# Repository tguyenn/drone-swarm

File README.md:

# Drone Swarm

This project is going to be a fully DIY drone swarm project based around ESP32 connectivity. There will be an ESP32 based handheld controller that will connect to ESP32 based drones over ESPNOW.

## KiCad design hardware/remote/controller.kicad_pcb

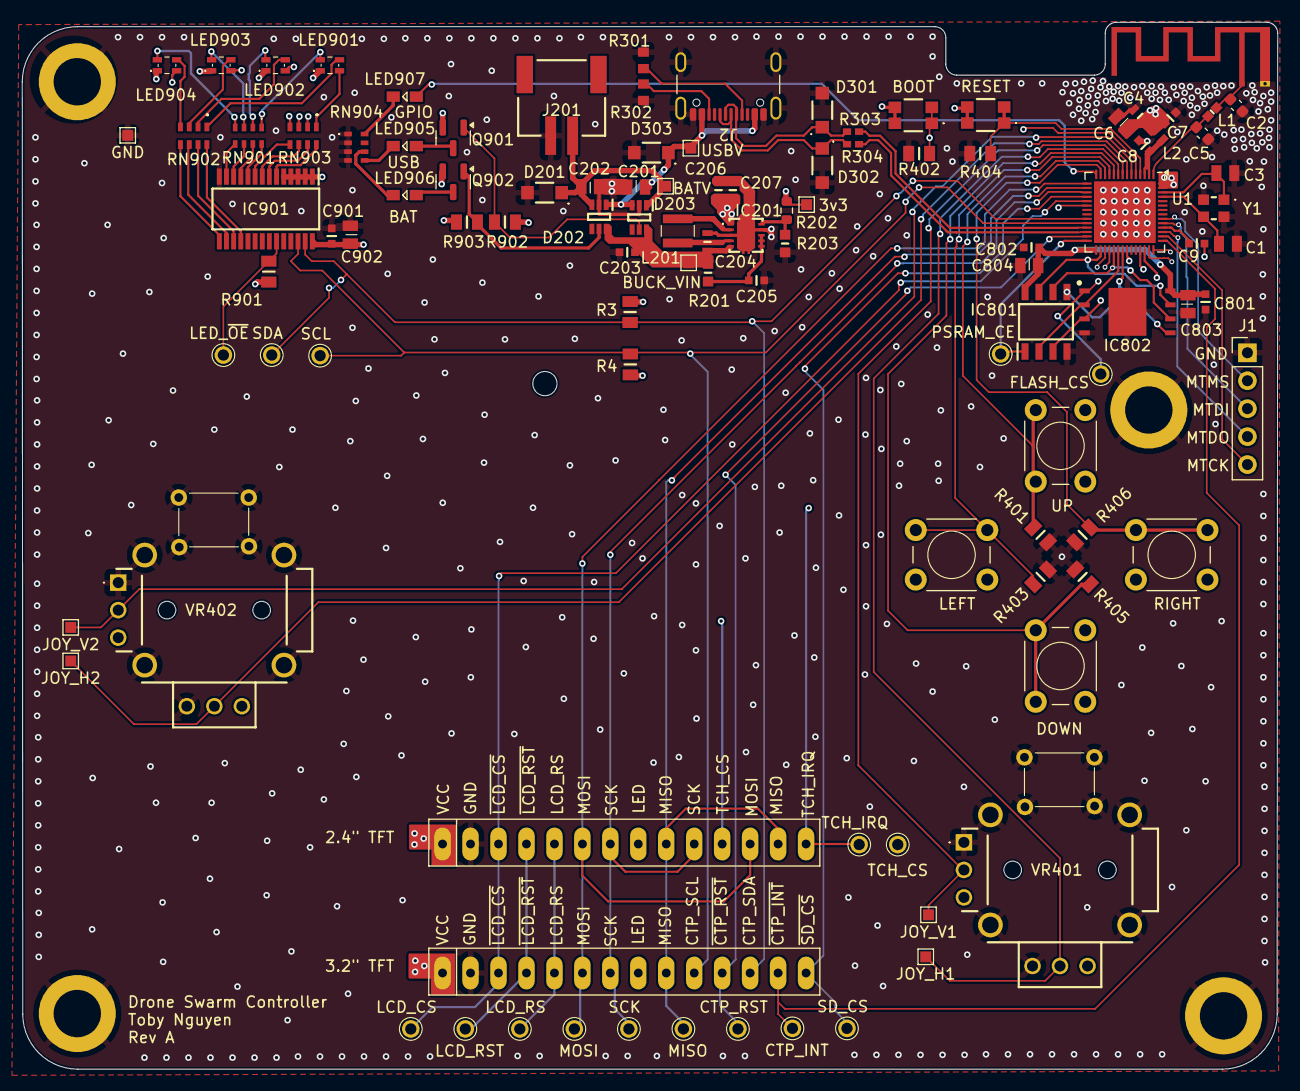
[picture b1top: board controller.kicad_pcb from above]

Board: 4 copper layers, 114.0 x 95.1 mm, 113 parts (0 on the bottom side), 90 nets.

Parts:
AE1: Antenna_Chip; Texas_SWRA117D_2.4GHz_Left
C1, C3: 10p; CAPC2013X94N
C2, C5: 1p8; C_0603_1608Metric
C4, C204, C206, C207: 10u; CAPC1608X80N
C6, C201, C202, C803, C804, C902: 1u; CAPC2012X135N
C7, C8, C9, C203, C205, C801, C802, C901: u1; MAJx16
D201, D301, D302, D303: SMF5.0A_R1_00001; SMF50A_R1_00001
D202, D203: LM66100DCKR; SOP65P210X110-6N
H101: MountingHole; MountingHole_2.2mm_M2_DIN965
H102, H103, H104, H105: MountingHole_Pad; MountingHole_4.3mm_M4_ISO14580_Pad
IC201: TPS63000IDRCRQ1
IC801: 4677; SOIC127P600X175-8N
IC802: W25Q256JVEIQ; SON127P800X600X80-9N-D
IC901: PCA9685PW_Q900,118; SOP65P640X110-28N
J1: Conn_01x05_Pin; PinHeader_1x05_P2.54mm_Vertical
J2: USB_C_Receptacle_USB2.0_16P; USB_C_Receptacle_GCT_USB4105-xx-A_16P_TopMnt_Horizontal
J201: JST-PH Conn; 1769
L1: 3nH; INDC1006X65N
L2: 2nH; WE-KI_0603A30
L201: 2u2; NRS3015T2R2MNGHV
LED901, LED902, LED903, LED904: SM0605RGB
LED905, LED906, LED907: Orange; LEDM2214X140N
NT201: NetTie; NetTie-2_Pad0.3mm
Q901, Q902: IRLML6402TRPBF; SOT-23
R3, R4, R401, R402, R403, R404, R405, R406, R901, R902, R903: 10k; RESC2012X60N
R201: 100; RESC1608X55N
R202: 1M; R_0603_1608Metric
R203: 200k; RESC1608X55N
R301, R302: 5k1; RESC1608X50N
R303, R304: 27; RESC1005X40N
RN901, RN904: 150 Ohms; EXBV8V151JV
RN902, RN903: 100 Ohms; EXBU38
S401: BOOT; TL1030AF500AQJ
S402: RESET; TL1030AF500AQJ
SW401: UP; SW_PUSH_6mm
SW402: LEFT; SW_PUSH_6mm
SW403: DOWN; SW_PUSH_6mm
SW404: RIGHT; SW_PUSH_6mm
TP3: MOSI; 5000
TP5: SDA; 5000
TP6: MISO; 5000
TP8: SCL; 5000
TP9: SCK; 5000
TP10: CTP_RST; 5000
TP11: SD_CS; 5000
TP12: CTP_INT; 5000
TP13: LCD_CS; 5000
TP14: LED_~{OE}; 5000
TP15: LCD_RST; 5000
TP16: LCD_RS; 5000
TP17: TCH_CS; 5000
TP18: TCH_IRQ; 5000
TP201: BATV; TestPoint_Pad_1.0x1.0mm
TP202: GND; TestPoint_Pad_1.0x1.0mm
TP203: 3v3; TestPoint_Pad_1.0x1.0mm
TP204: USBV; TestPoint_Pad_1.0x1.0mm
TP205: BUCK_VIN; TestPoint_Pad_1.0x1.0mm
TP401: JOY_V1; TestPoint_Pad_1.0x1.0mm
TP402: JOY_H1; TestPoint_Pad_1.0x1.0mm
TP403: JOY_V2; TestPoint_Pad_1.0x1.0mm
TP404: JOY_H2; TestPoint_Pad_1.0x1.0mm
TP801: PSRAM_CE; 5000
TP802: FLASH_CS; 5000
U1: ESP32-S3; QFN-56-1EP_7x7mm_P0.4mm_EP5.6x5.6mm
U501, U502: 3.2inch_IPS_SPI_Module_ILI9341; TFT-320x240
VR401, VR402: RKJXV1224005
Y1: FH4000074Z

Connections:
+3V3: C4.1, C6.1, C7.1, C9.1, C206.1, C207.1, C901.1, C902.1, IC201.1 (VOUT), IC901.1 (A0), IC901.2 (A1), IC901.3 (A2), IC901.4 (A3), IC901.5 (A4), IC901.28 (VDD), L2.1, LED901.1 (ANODE), LED902.1 (ANODE), LED903.1 (ANODE), LED904.1 (ANODE), Q901.2 (S), Q902.2 (S), R3.2, R4.2, R202.1, R901.1, R902.2, R903.2, S401.2, S402.2, SW401.2, SW402.2, SW403.2, SW404.2, TP203.1, U1.20 (VDD3P3_RTC), U1.55 (VDDA), U1.56 (VDDA), U501.1 (VCC), U502.1 (VCC), VR401.A3 (CW_1), VR401.B3 (CW_2), VR402.A3 (CW_1), VR402.B3 (CW_2)
/ESP32/BUT_JOY.BUT_BOOT: R402.1, S401.1, U1.5 (GPIO0/BOOT)
/ESP32/BUT_JOY.BUT_DOWN: R405.1, SW403.1, U1.10 (GPIO5/ADC1_CH4)
/ESP32/BUT_JOY.BUT_LEFT: R403.1, SW402.1, U1.11 (GPIO6/ADC1_CH5)
/ESP32/BUT_JOY.BUT_RESET: R404.1, S402.1, U1.4 (CHIP_PU/RESET)
/ESP32/BUT_JOY.BUT_RIGHT: R406.1, SW404.1, U1.13 (GPIO8/ADC1_CH7)
/ESP32/BUT_JOY.BUT_UP: R401.1, SW401.1, U1.12 (GPIO7/ADC1_CH6)
/ESP32/BUT_JOY.JOY1_H: TP402.1, U1.9 (GPIO4/ADC1_CH3), VR401.B2 (WIPER_2)
/ESP32/BUT_JOY.JOY1_V: TP401.1, U1.8 (GPIO3/ADC1_CH2), VR401.A2 (WIPER_1)
/ESP32/BUT_JOY.JOY2_H: TP404.1, U1.7 (GPIO2/ADC1_CH1), VR402.B2 (WIPER_2)
/ESP32/BUT_JOY.JOY2_V: TP403.1, U1.6 (GPIO1/ADC1_CH0), VR402.A2 (WIPER_1)
/ESP32/I2C_CTP_LED.CTP_INT: TP12.1, U1.43 (GPIO38), U501.13 (~CTP_INT)
/ESP32/I2C_CTP_LED.CTP_RST: TP10.1, U1.27 (GPIO21), U501.11 (~CTP_RST)
/ESP32/I2C_CTP_LED.SCL: IC901.26 (SCL), R4.1, TP8.1, U1.24 (GPIO18/ADC2_CH7), U501.10 (CTP_SCL)
/ESP32/I2C_CTP_LED.SDA: IC901.27 (SDA), R3.1, TP5.1, U1.23 (GPIO17/ADC2_CH6), U501.12 (CTP_SDA)
/ESP32/I2C_CTP_LED.~OE: IC901.23 (~OE), R901.2, TP14.1, U1.36 (SPICLK_N/GPIO48)
/ESP32/LED_GPIO: LED907.2 (A), U1.14 (GPIO9/ADC1_CH8)
/ESP32/MEM.SCK: IC801.6 (SCLK), IC802.6 (CLK), U1.33 (SPICLK/GPIO30)
/ESP32/MEM.SIO0: IC801.5 (SI/SIO[0]), IC802.5 (DI_(IO0)), U1.35 (SPID/GPIO32)
/ESP32/MEM.SIO1: IC801.2 (SO/SIO[1]), IC802.2 (DO_(IO1)_1), U1.34 (SPIQ/GPIO31)
/ESP32/MEM.SIO2: IC801.3 (SIO[2]), IC802.3 (DO_(IO1)_2), U1.31 (SPIWP/GPIO28)
/ESP32/MEM.SIO3: IC801.7 (SIO[3]), IC802.7 (IO3), U1.30 (SPIHD/GPIO27)
/ESP32/MEM.~CE: IC801.1 (CE#), TP801.1, U1.28 (SPI_CS1/GPIO26)
/ESP32/MEM.~CS: IC802.1 (/CS), TP802.1, U1.32 (SPICS0/GPIO29)
/ESP32/MTCK: J1.5, U1.44 (MTCK/JTAG/GPIO39)
/ESP32/MTDI: J1.3, U1.47 (MTDI/JTAG/GPIO41)
/ESP32/MTDO: J1.4, U1.45 (MTDO/JTAG/GPIO40)
/ESP32/MTMS: J1.2, U1.48 (MTMS/JTAG/GPIO42)
/ESP32/SPI_LCD_SD.LCD_CS: TP13.1, U1.19 (GPIO14/ADC2_CH3), U501.3 (~LCD_CS), U502.3 (~LCD_CS)
/ESP32/SPI_LCD_SD.LCD_RS: TP16.1, U1.42 (GPIO37), U501.5 (LCD_RS), U502.5 (LCD_RS)
/ESP32/SPI_LCD_SD.LCD_RST: TP15.1, U1.41 (GPIO36), U501.4 (~LCD_RST), U502.4 (~LCD_RST)
/ESP32/SPI_LCD_SD.MISO: TP6.1, U1.16 (GPIO11/ADC2_CH0), U501.9 (MISO), U502.9 (MISO), U502.13 (T_DO)
/ESP32/SPI_LCD_SD.MOSI: TP3.1, U1.15 (GPIO10/ADC1_CH9), U501.6 (MOSI), U502.6 (MOSI), U502.12 (T_DIN)
/ESP32/SPI_LCD_SD.SCK: TP9.1, U1.17 (GPIO12/ADC2_CH1), U501.7 (SCK), U502.7 (SCK), U502.10 (T_CLK)
/ESP32/SPI_LCD_SD.SD_CS: TP11.1, U1.18 (GPIO13/ADC2_CH2), U501.14 (~SD_CS)
/ESP32/SPI_LCD_SD.TCH_CS: TP17.1, U1.40 (GPIO35), U502.11 (T_CS)
/ESP32/SPI_LCD_SD.TCH_IRQ: TP18.1, U1.39 (GPIO34), U502.14 (T_IRQ)
/ESP32/USB+: R304.2, U1.26 (GPIO20/USB_D+/ADC2_CH9)
/ESP32/USB-: R303.2, U1.25 (GPIO19/USB_D-/ADC2_CH8)
/LEDS/B1: LED901.2 (C_BLUE), RN903.1
/LEDS/B2: LED902.2 (C_BLUE), RN903.2
/LEDS/B3: LED903.2 (C_BLUE), RN903.3
/LEDS/B4: LED904.2 (C_BLUE), RN903.4
/LEDS/BAT_ST: D203.5 (ST), Q901.1 (G), R902.1
/LEDS/C_BLU1: IC901.6 (LED0), RN903.8
/LEDS/C_BLU2: IC901.7 (LED1), RN903.7
/LEDS/C_BLU3: IC901.8 (LED2), RN903.6
/LEDS/C_BLU4: IC901.9 (LED3), RN903.5
/LEDS/C_GRN1: IC901.18 (LED11), RN902.8
/LEDS/C_GRN2: IC901.17 (LED10), RN902.7
/LEDS/C_GRN3: IC901.16 (LED9), RN902.6
/LEDS/C_GRN4: IC901.15 (LED8), RN902.5
/LEDS/C_RED1: IC901.10 (LED4), RN901.8
/LEDS/C_RED2: IC901.11 (LED5), RN901.7
/LEDS/C_RED3: IC901.12 (LED6), RN901.6
/LEDS/C_RED4: IC901.13 (LED7), RN901.5
/LEDS/G1: LED901.4 (C_GREEN), RN902.1
/LEDS/G2: LED902.4 (C_GREEN), RN902.2
/LEDS/G3: LED903.4 (C_GREEN), RN902.3
/LEDS/G4: LED904.4 (C_GREEN), RN902.4
/LEDS/R1: LED901.3 (C_RED), RN901.1
/LEDS/R2: LED902.3 (C_RED), RN901.2
/LEDS/R3: LED903.3 (C_RED), RN901.3
/LEDS/R4: LED904.3 (C_RED), RN901.4
/LEDS/USBC_ST: D202.5 (ST), Q902.1 (G), R903.1
/POWER/BAT_VBUS: C202.1, D201.1 (K), D202.3 (~CE), D203.1 (VIN), J201.1, TP201.1
/POWER/BUCK_VIN: C203.1, C204.1, D202.6 (VOUT), D203.6 (VOUT), IC201.5 (VIN), R201.1, TP205.1
/POWER/USBC_VBUS: C201.1, D202.1 (VIN), D203.3 (~CE), D303.1 (K), J2.A4 (VBUS), J2.A9 (VBUS), J2.B4 (VBUS), J2.B9 (VBUS), TP204.1
/USBC/CC1: J2.A5 (CC1), R301.1
/USBC/CC2: J2.B5 (CC2), R302.1
/USBC/D+: D302.1 (K), J2.A6 (D+), J2.B6 (D+), R304.1
/USBC/D-: D301.1 (K), J2.A7 (D-), J2.B7 (D-), R303.1
GND: AE1.2 (PCB_Trace), C1.2, C2.2, C3.2, C4.2, C5.2, C6.2, C7.2, C8.2, C201.2, C202.2, C203.2, C205.2, C801.2, C802.2, C803.2, C804.2, C901.2, C902.2, D201.2 (A), D202.2 (GND), D203.2 (GND), D301.2 (A), D302.2 (A), D303.2 (A), H102.1, H103.1, H104.1, H105.1, IC201.9 (GND), IC801.4 (VSS), IC802.4 (GND), IC802.9 (EP), IC901.14 (VSS), J1.1, J2.A1 (GND), J2.A12 (GND), J2.B1 (GND), J2.B12 (GND), J2.S1 (SHIELD), J201.2, NT201.1, R203.2, R301.2, R302.2, R401.2, R402.2, R403.2, R404.2, R405.2, R406.2, RN904.1, RN904.2, RN904.3, RN904.4, TP202.1, U1.57 (GND), U501.2 (GND), U502.2 (GND), VR401.1 (MH1), VR401.2 (MH2), VR401.3 (MH3), VR401.4 (MH4), VR401.5 (BUT_0), VR401.6 (BUT_1), VR401.A1 (CCW_1), VR401.B1 (CCW_2), VR402.1 (MH1), VR402.2 (MH2), VR402.3 (MH3), VR402.4 (MH4), VR402.5 (BUT_0), VR402.6 (BUT_1), VR402.A1 (CCW_1), VR402.B1 (CCW_2), Y1.2 (GND), Y1.4 (GND)
GNDPWR: C204.2, C206.2, C207.2, IC201.3 (PGND_1), IC201.11 (PGND_2), IC201.12 (PGND_3), IC201.13 (PGND_4), IC201.14 (PGND_5), IC201.15 (PGND_6), NT201.2
unnamed: AE1.1 (FEED), C2.1, L1.1
unnamed: C205.1, IC201.6 (EN), IC201.7 (PS/SYNC), IC201.8 (VINA), R201.2
unnamed: IC201.10 (FB), R202.2, R203.1
unnamed: IC201.4 (L1), L201.1
unnamed: IC201.2 (L2), L201.2
unnamed: LED905.2 (A), Q901.3 (D)
unnamed: LED905.1 (K), RN904.5
unnamed: LED906.2 (A), Q902.3 (D)
unnamed: LED906.1 (K), RN904.6
unnamed: LED907.1 (K), RN904.8
unnamed: C5.1, L1.2, U1.1 (LNA_IN/RF)
unnamed: C9.2, U1.46 (VDD3P3_CPU)
unnamed: C1.1, U1.53 (XTAL_N), Y1.3 (XOUT)
unnamed: C3.1, U1.54 (XTAL_P), Y1.1 (XIN)
VDD3P3: C8.1, L2.2, U1.2 (VDD3P3), U1.3 (VDD3P3)
VDD_SPI: C801.1, C802.1, C803.1, C804.1, IC801.8 (VCC), IC802.8 (VCC), U1.29 (VDD_SPI)

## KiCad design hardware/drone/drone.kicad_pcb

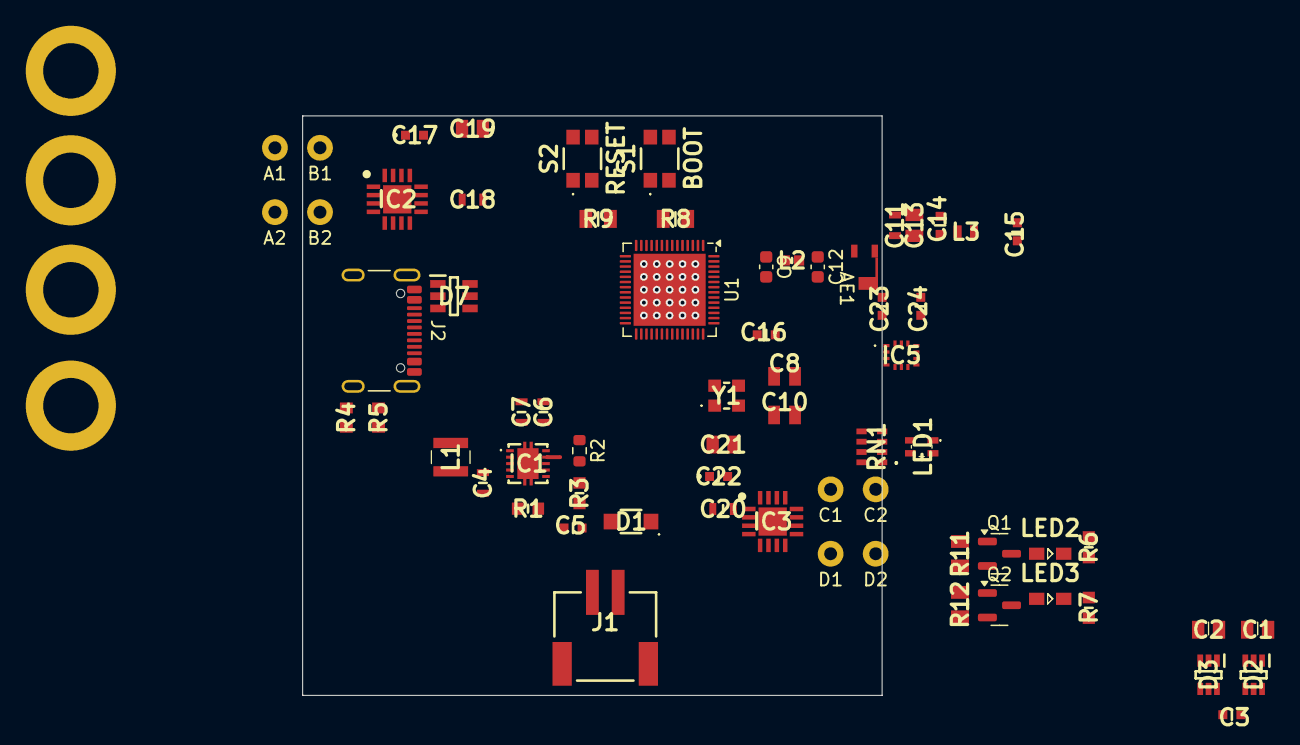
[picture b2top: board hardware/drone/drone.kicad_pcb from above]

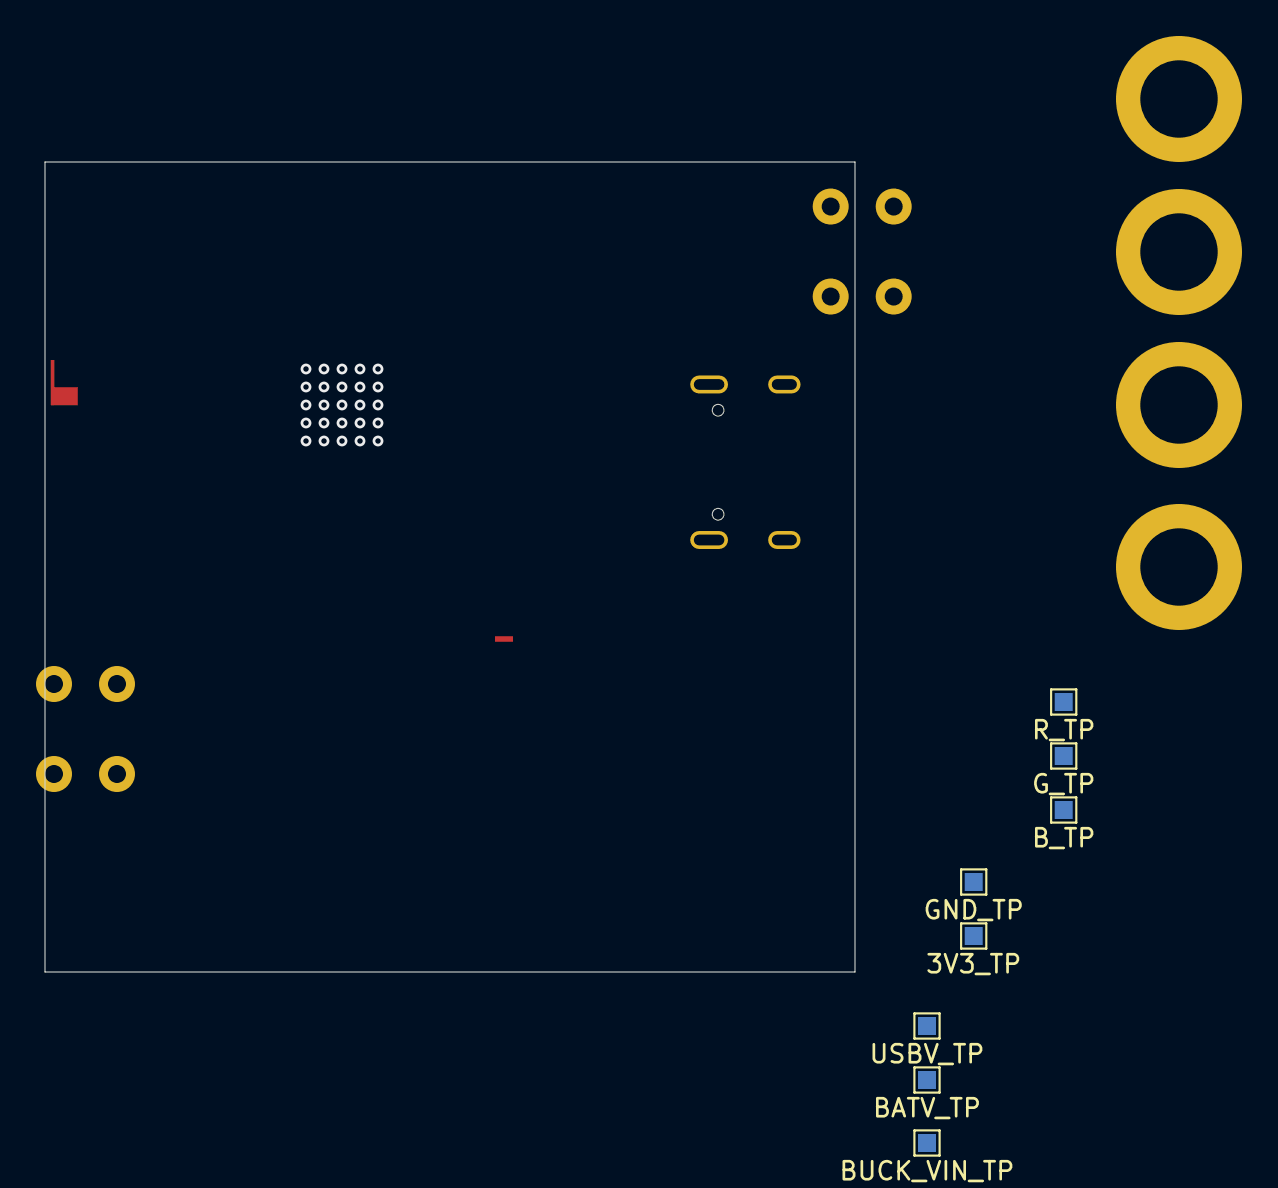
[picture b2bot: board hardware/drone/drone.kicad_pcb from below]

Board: 4 copper layers, 45.0 x 45.0 mm, 80 parts (8 on the bottom side), 62 nets, no tracks yet.

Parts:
AE1: Antenna_Chip; AANI-CH-0133
C1, C2, C13: 1u; CAPC2012X135N
C3, C5, C14, C15, C16, C23, C24: u1; MAJx16
C4, C6, C7, C11, C18, C20: 10u; CAPC1608X80N
C8, C10: 10p; CAPC2013X94N
C9, C12: 1p8; C_0603_1608Metric
C17, C22: 2u2; MBASx168
C19, C21: 10n; CAPC2012X90N
D1: SMF5.0A_R1_00001; SMF50A_R1_00001
D2, D3: LM66100DCKR; SOP65P210X110-6N
D7: USBLC6-4SC6Y; SOT95P280X145-6N
H2, H3, H4, H5: MountingHole_Pad; MountingHole_4.3mm_M4_ISO14580_Pad
IC1: TPS63000IDRCRQ1
IC2, IC3: DRV8833RTYR; QFN65P400X400X80-17N-D
IC5: BMI323
J1: 1769
J2: USB_C_Receptacle_GCT_USB4105-xx-A_16P_TopMnt_Horizontal
L1: 2u2; NRS3015T2R2MNGHV
L2: 3nH; INDC1006X65N
L3: 2nH; WE-KI_0603A30
LED1: SM0605RGB
LED2, LED3: LO_M676-Q2S1-24-Z; LEDM2214X140N
NT1: NetTie; custom_net_tie
Q1, Q2: IRLML6402TRPBF; SOT-23
R1, R6, R7: 100; RESC1608X55N
R2: 1M; R_0603_1608Metric
R3: 200k; RESC1608X55N
R4, R5: 5k1; RESC1608X50N
R8, R9, R11, R12: 10k; RESC2012X60N
RN1: 100 Ohms; EXBU38
S1: BOOT; TL1030AF500AQJ
S2: RESET; TL1030AF500AQJ
TP1: USBV_TP; TestPoint_Pad_1.0x1.0mm
TP2: BATV_TP; TestPoint_Pad_1.0x1.0mm
TP3: BUCK_VIN_TP; TestPoint_Pad_1.0x1.0mm
TP4: GND_TP; TestPoint_Pad_1.0x1.0mm
TP5: 3V3_TP; TestPoint_Pad_1.0x1.0mm
TP6: R_TP; TestPoint_Pad_1.0x1.0mm
TP7: G_TP; TestPoint_Pad_1.0x1.0mm
TP8: B_TP; TestPoint_Pad_1.0x1.0mm
TP9: A1; Motor solder point
TP10: A2; Motor solder point
TP11: B1; Motor solder point
TP12: B2; Motor solder point
TP13: C1; Motor solder point
TP14: D1; Motor solder point
TP15: C2; Motor solder point
TP16: D2; Motor solder point
U1: ESP32-S3; QFN-56-1EP_7x7mm_P0.4mm_EP5.6x5.6mm
Y1: FH4000074Z

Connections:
+3V3: C6.1, C7.1, C11.1, C13.1, C14.1, C16.1, C23.1, C24.1, IC1.1 (VOUT), IC5.5 (VDDIO), IC5.8 (VDD), L3.1, LED1.1 (ANODE), Q1.2 (S), Q2.2 (S), R2.1, R11.2, R12.2, S1.2, S2.2, TP5.1, U1.20 (VDD3P3_RTC), U1.55 (VDDA), U1.56 (VDDA)
+BATT: C2.1, C18.1, C19.1, C20.1, C21.1, D1.1 (K), D2.3 (~CE), D3.1 (VIN), IC2.10 (VM), IC3.10 (VM), J1.1, TP2.1
/ESP32/BOOT: R8.1, S1.1, U1.5 (GPIO0/BOOT)
/ESP32/D+: D7.4 (I/O3), U1.26 (GPIO20/USB_D+/ADC2_CH9)
/ESP32/D-: D7.6 (I/O4), U1.25 (GPIO19/USB_D-/ADC2_CH8)
/ESP32/IMU_CS: IC5.12 (CSB), U1.16 (GPIO11/ADC2_CH0)
/ESP32/INT1: IC5.4 (INT1), U1.23 (GPIO17/ADC2_CH6)
/ESP32/INT2: IC5.9 (INT2), U1.24 (GPIO18/ADC2_CH7)
/ESP32/MD.AIN1: IC2.14 (AIN1), U1.7 (GPIO2/ADC1_CH1)
/ESP32/MD.AIN2: IC2.13 (AIN2), U1.9 (GPIO4/ADC1_CH3)
/ESP32/MD.BIN1: IC2.7 (BIN1), U1.10 (GPIO5/ADC1_CH4)
/ESP32/MD.BIN2: IC2.8 (BIN2), U1.11 (GPIO6/ADC1_CH5)
/ESP32/MD.CIN1: IC3.14 (AIN1), U1.12 (GPIO7/ADC1_CH6)
/ESP32/MD.CIN2: IC3.13 (AIN2), U1.13 (GPIO8/ADC1_CH7)
/ESP32/MD.DIN1: IC3.7 (BIN1), U1.14 (GPIO9/ADC1_CH8)
/ESP32/MD.DIN2: IC3.8 (BIN2), U1.15 (GPIO10/ADC1_CH9)
/ESP32/RESET: R9.1, S2.1, U1.4 (CHIP_PU/RESET)
/ESP32/RGB.B: RN1.6, TP8.1
/ESP32/RGB.G: RN1.7, TP7.1
/ESP32/RGB.R: RN1.8, TP6.1
/ESP32/SPI.MISO: IC5.1 (SDO/MISO), U1.17 (GPIO12/ADC2_CH1)
/ESP32/SPI.MOSI: IC5.14 (SDX/MOSI), U1.18 (GPIO13/ADC2_CH2)
/ESP32/SPI.SCK: IC5.13 (SCX), U1.19 (GPIO14/ADC2_CH3)
/LEDS/BAT_ST: D3.5 (ST), Q1.1 (G), R11.1
/LEDS/USBC_ST: D2.5 (ST), Q2.1 (G), R12.1
/MOTORS/A1: IC2.16 (AOUT1), TP9.1
/MOTORS/A2: IC2.2 (AOUT2), TP10.1
/MOTORS/B1: IC2.5 (BOUT1), TP11.1
/MOTORS/B2: IC2.3 (BOUT2), TP12.1
/MOTORS/C1: IC3.16 (AOUT1), TP13.1
/MOTORS/C2: IC3.2 (AOUT2), TP15.1
/MOTORS/D1: IC3.5 (BOUT1), TP14.1
/MOTORS/D2: IC3.3 (BOUT2), TP16.1
/POWER/BUCK_VIN: C3.1, C4.1, D2.6 (VOUT), D3.6 (VOUT), IC1.5 (VIN), R1.1, TP3.1
/POWER/USBC_VBUS: C1.1, D2.1 (VIN), D3.3 (~CE), D7.5 (VBUS), J2.A4 (VBUS), J2.A9 (VBUS), J2.B4 (VBUS), J2.B9 (VBUS), TP1.1
/USBC/CC1: J2.A5 (CC1), R4.1
/USBC/CC2: J2.B5 (CC2), R5.1
/USBC/USB+: D7.1 (I/O1), J2.A6 (D+), J2.B6 (D+)
/USBC/USB-: D7.3 (I/O2), J2.A7 (D-), J2.B7 (D-)
GND: C1.2, C2.2, C3.2, C5.2, C8.2, C9.2, C10.2, C11.2, C12.2, C13.2, C14.2, C15.2, C17.1, C18.2, C20.2, C22.1, C23.2, C24.2, D1.2 (A), D2.2 (GND), D3.2 (GND), D7.2 (GND), H2.1, H3.1, H4.1, H5.1, IC1.9 (GND), IC2.1 (AISEN), IC2.4 (BISEN), IC2.11 (GND_1), IC2.17 (GND_2), IC3.1 (AISEN), IC3.4 (BISEN), IC3.11 (GND_1), IC3.17 (GND_2), IC5.6 (GNDIO), IC5.7 (GND), J1.2, J1.3, J1.4, J2.A1 (GND), J2.A12 (GND), J2.B1 (GND), J2.B12 (GND), J2.S1 (SHIELD), NT1.1, R3.2, R4.2, R5.2, R6.2, R7.2, R8.2, R9.2, TP4.1, U1.57 (GND), Y1.2 (GND), Y1.4 (GND)
GNDPWR: C4.2, C6.2, C7.2, IC1.3 (PGND_1), IC1.11 (PGND_2), IC1.12 (PGND_3), IC1.13 (PGND_4), IC1.14 (PGND_5), IC1.15 (PGND_6), NT1.2
unnamed: AE1.1 (FEED), C9.1, L2.1
unnamed: C5.1, IC1.6 (EN), IC1.7 (PS/SYNC), IC1.8 (VINA), R1.2
unnamed: IC1.10 (FB), R2.2, R3.1
unnamed: IC1.4 (L1), L1.1
unnamed: IC1.2 (L2), L1.2
unnamed: C19.2, IC2.9 (VCP)
unnamed: C17.2, IC2.12 (VINT)
unnamed: C21.2, IC3.9 (VCP)
unnamed: C22.2, IC3.12 (VINT)
unnamed: LED1.2 (C_BLUE), RN1.3
unnamed: LED1.4 (C_GREEN), RN1.2
unnamed: LED1.3 (C_RED), RN1.1
unnamed: LED2.2 (A), Q1.3 (D)
unnamed: LED2.1 (K), R6.1
unnamed: LED3.2 (A), Q2.3 (D)
unnamed: LED3.1 (K), R7.1
unnamed: C12.1, L2.2, U1.1 (LNA_IN/RF)
unnamed: C16.2, U1.46 (VDD3P3_CPU)
unnamed: C8.1, U1.53 (XTAL_N), Y1.3 (XOUT)
unnamed: C10.1, U1.54 (XTAL_P), Y1.1 (XIN)
VDD3P3: C15.1, L3.2, U1.2 (VDD3P3), U1.3 (VDD3P3)

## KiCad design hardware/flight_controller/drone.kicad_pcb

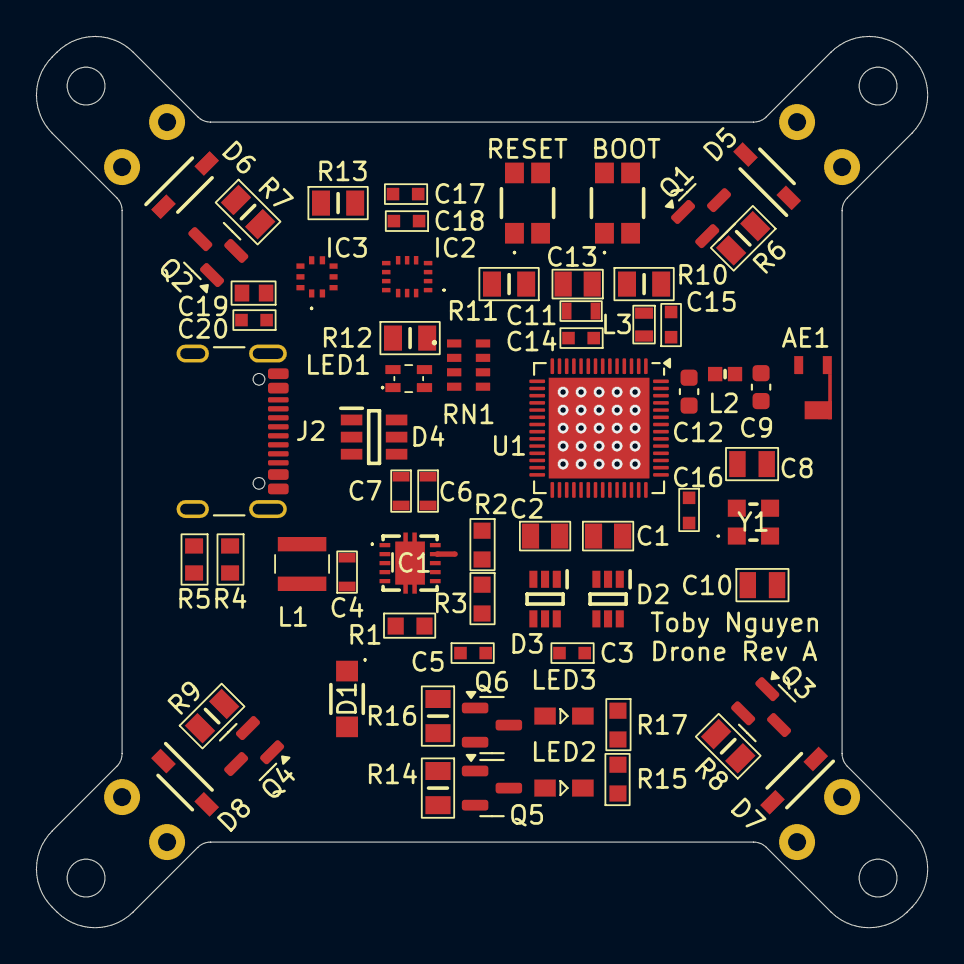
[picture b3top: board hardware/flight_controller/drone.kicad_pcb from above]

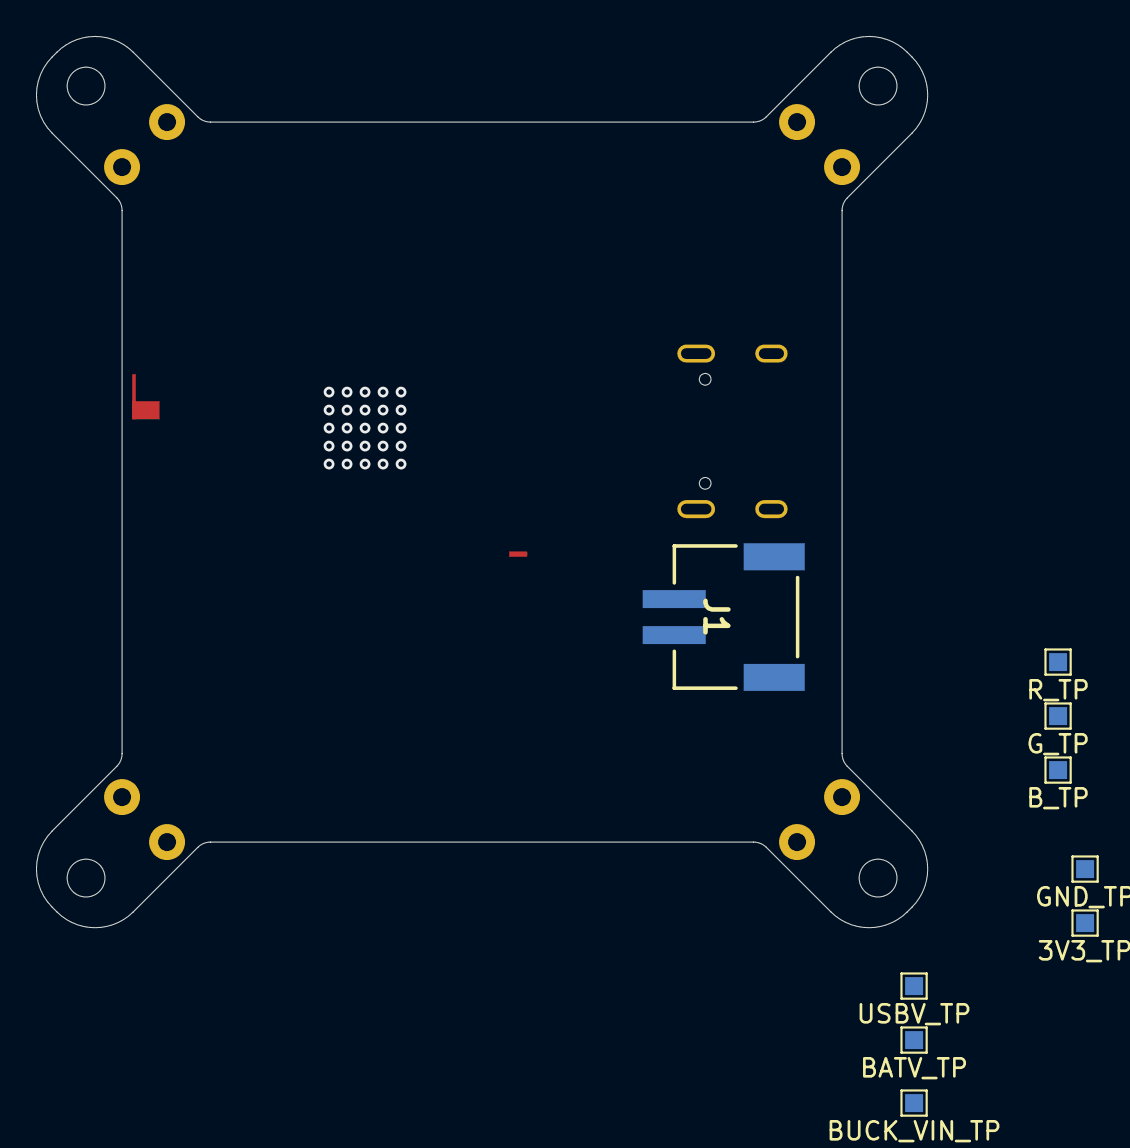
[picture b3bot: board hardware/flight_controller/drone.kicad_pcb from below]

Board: 4 copper layers, 49.5 x 49.5 mm, 89 parts (9 on the bottom side), 51 nets, no tracks yet.

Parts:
AE1: Antenna_Chip; AANI-CH-0133
C1, C2, C13: 1u; CAPC2012X135N
C3, C5, C14, C15, C16, C17, C18, C20: u1; MAJx16
C4, C6, C7, C11: 10u; CAPC1608X80N
C8, C10: 10p; CAPC2013X94N
C9, C12: 1p8; C_0603_1608Metric
C19: 4u7; CAPC1608X90N
D1: SMF5.0A_R1_00001; SMF50A_R1_00001
D2, D3: LM66100DCKR; SOP65P210X110-6N
D4: USBLC6-4SC6Y; SOT95P280X145-6N
D5, D6, D7, D8: 1N4148WQ-7-F; SOD3716X145N
H1, H2, H3, H4: MountingHole; MountingHole_2.1mm
IC1: TPS63000IDRCRQ1
IC2: BMI323
IC3: LPS25HBTR
J1: 1769
J2: USB_C_Receptacle_GCT_USB4105-xx-A_16P_TopMnt_Horizontal
L1: 2u2; NRS3015T2R2MNGHV
L2: 3nH; INDC1006X65N
L3: 2nH; WE-KI_0603A30
LED1: SM0605RGB
LED2, LED3: LO_M676-Q2S1-24-Z; LEDM2214X140N
NT1: NetTie; custom_net_tie
Q1, Q2, Q3, Q4: IRLML6344; SOT-23
Q5, Q6: IRLML6402TRPBF; SOT-23
R1, R15, R17: 100; RESC1608X55N
R2: 1M; RESC1608X55N
R3: 200k; RESC1608X55N
R4, R5: 5k1; RESC1608X50N
R6, R7, R8, R9, R10, R11, R12, R13, R14, R16: 10k; RESC2012X60N
RN1: 100 Ohms; EXBU38
S1: BOOT; TL1030AF500AQJ
S2: RESET; TL1030AF500AQJ
TP1: GND_TP; TestPoint_Pad_1.0x1.0mm
TP2: 3V3_TP; TestPoint_Pad_1.0x1.0mm
TP3: USBV_TP; TestPoint_Pad_1.0x1.0mm
TP4: BATV_TP; TestPoint_Pad_1.0x1.0mm
TP5: BUCK_VIN_TP; TestPoint_Pad_1.0x1.0mm
TP6: A-; Motor solder point
TP7: A+; Motor solder point
TP8: B-; Motor solder point
TP9: B+; Motor solder point
TP10: C-; Motor solder point
TP11: C+; Motor solder point
TP12: D-; Motor solder point
TP13: D+; Motor solder point
TP14: R_TP; TestPoint_Pad_1.0x1.0mm
TP15: G_TP; TestPoint_Pad_1.0x1.0mm
TP16: B_TP; TestPoint_Pad_1.0x1.0mm
U1: ESP32-S3; QFN-56-1EP_7x7mm_P0.4mm_EP5.6x5.6mm
Y1: FH4000074Z

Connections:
+3V3: C6.1, C7.1, C11.1, C13.1, C14.1, C16.1, C17.1, C18.1, C19.1, C20.1, IC1.1 (VOUT), IC2.5 (VDDIO), IC2.8 (VDD), IC3.1 (VDD_IO), IC3.10 (VDD), L3.1, LED1.1 (ANODE), Q5.2 (S), Q6.2 (S), R2.1, R12.2, R13.2, R14.2, R16.2, S1.2, S2.2, TP2.1, U1.20 (VDD3P3_RTC), U1.46 (VDD3P3_CPU), U1.55 (VDDA), U1.56 (VDDA)
+BATT: C2.1, D1.1 (K), D2.3 (~CE), D3.1 (VIN), D5.1 (K), D6.1 (K), D7.1 (K), D8.1 (K), J1.1, TP4.1, TP7.1, TP9.1, TP11.1, TP13.1
/ESP32/BARO.CS: IC3.6 (CS), R13.1, U1.36 (SPICLK_N/GPIO48)
/ESP32/BARO.INT: IC3.7 (INT_DRDY), U1.37 (SPICLK_P/GPIO47)
/ESP32/BOOT: R10.1, S1.1, U1.5 (GPIO0/BOOT)
/ESP32/D+: D4.4 (I/O3), U1.26 (GPIO20/USB_D+/ADC2_CH9)
/ESP32/D-: D4.6 (I/O4), U1.25 (GPIO19/USB_D-/ADC2_CH8)
/ESP32/IMU.INT1: IC2.4 (INT1), U1.23 (GPIO17/ADC2_CH6)
/ESP32/IMU.INT2: IC2.9 (INT2), U1.24 (GPIO18/ADC2_CH7)
/ESP32/IMU_CS: IC2.12 (CSB), R12.1, U1.16 (GPIO11/ADC2_CH0)
/ESP32/MOTORS.MA: Q1.1 (G), R6.2, U1.6 (GPIO1/ADC1_CH0)
/ESP32/MOTORS.MB: Q2.1 (G), R7.2, U1.7 (GPIO2/ADC1_CH1)
/ESP32/MOTORS.MC: Q3.1 (G), R8.2, U1.8 (GPIO3/ADC1_CH2)
/ESP32/MOTORS.MD: Q4.1 (G), R9.2, U1.9 (GPIO4/ADC1_CH3)
/ESP32/RESET: R11.1, S2.1, U1.4 (CHIP_PU/RESET)
/ESP32/RGB.B: RN1.5, TP16.1, U1.41 (GPIO36)
/ESP32/RGB.G: RN1.6, TP15.1, U1.40 (GPIO35)
/ESP32/RGB.R: RN1.7, TP14.1, U1.39 (GPIO34)
/ESP32/SPI.MISO: IC2.1 (SDO/MISO), IC3.5 (SDO/_SA0), U1.17 (GPIO12/ADC2_CH1)
/ESP32/SPI.MOSI: IC2.14 (SDX/MOSI), IC3.4 (SDA/SDI/SDO), U1.18 (GPIO13/ADC2_CH2)
/ESP32/SPI.SCK: IC2.13 (SCX), IC3.2 (SCL/_SPC), U1.19 (GPIO14/ADC2_CH3)
/LEDS/BAT_ST: D3.5 (ST), Q5.1 (G), R14.1
/LEDS/USBC_ST: D2.5 (ST), Q6.1 (G), R16.1
/POWER/BUCK_VIN: C3.1, C4.1, D2.6 (VOUT), D3.6 (VOUT), IC1.5 (VIN), R1.1, TP5.1
/POWER/USBC_VBUS: C1.1, D2.1 (VIN), D3.3 (~CE), D4.5 (VBUS), J2.A4 (VBUS), J2.A9 (VBUS), J2.B4 (VBUS), J2.B9 (VBUS), TP3.1
/USBC/CC1: J2.A5 (CC1), R4.1
/USBC/CC2: J2.B5 (CC2), R5.1
/USBC/USB+: D4.1 (I/O1), J2.A6 (D+), J2.B6 (D+)
/USBC/USB-: D4.3 (I/O2), J2.A7 (D-), J2.B7 (D-)
GND: C1.2, C2.2, C3.2, C5.2, C8.2, C9.2, C10.2, C11.2, C12.2, C13.2, C14.2, C15.2, C16.2, C17.2, C18.2, C19.2, C20.2, D1.2 (A), D2.2 (GND), D3.2 (GND), D4.2 (GND), IC1.9 (GND), IC2.6 (GNDIO), IC2.7 (GND), IC3.3 (RES), IC3.8 (GND_1), IC3.9 (GND_2), J1.2, J1.3, J1.4, J2.A1 (GND), J2.A12 (GND), J2.B1 (GND), J2.B12 (GND), J2.S1 (SHIELD), NT1.1, Q1.2 (S), Q2.2 (S), Q3.2 (S), Q4.2 (S), R3.2, R4.2, R5.2, R6.1, R7.1, R8.1, R9.1, R10.2, R11.2, R15.2, R17.2, TP1.1, U1.57 (GND), Y1.2 (GND), Y1.4 (GND)
GNDPWR: C4.2, C6.2, C7.2, IC1.3 (PGND_1), IC1.11 (PGND_2), IC1.12 (PGND_3), IC1.13 (PGND_4), IC1.14 (PGND_5), IC1.15 (PGND_6), NT1.2
unnamed: AE1.1 (FEED), C9.1, L2.1
unnamed: D5.2 (A), Q1.3 (D), TP6.1
unnamed: D6.2 (A), Q2.3 (D), TP8.1
unnamed: D7.2 (A), Q3.3 (D), TP10.1
unnamed: D8.2 (A), Q4.3 (D), TP12.1
unnamed: C5.1, IC1.6 (EN), IC1.7 (PS/SYNC), IC1.8 (VINA), R1.2
unnamed: IC1.10 (FB), R2.2, R3.1
unnamed: IC1.4 (L1), L1.1
unnamed: IC1.2 (L2), L1.2
unnamed: LED1.2 (C_BLUE), RN1.3
unnamed: LED1.4 (C_GREEN), RN1.2
unnamed: LED1.3 (C_RED), RN1.1
unnamed: LED2.2 (A), Q5.3 (D)
unnamed: LED2.1 (K), R15.1
unnamed: LED3.2 (A), Q6.3 (D)
unnamed: LED3.1 (K), R17.1
unnamed: C12.1, L2.2, U1.1 (LNA_IN/RF)
unnamed: C8.1, U1.53 (XTAL_N), Y1.3 (XOUT)
unnamed: C10.1, U1.54 (XTAL_P), Y1.1 (XIN)
VDD3P3: C15.1, L3.2, U1.2 (VDD3P3), U1.3 (VDD3P3)

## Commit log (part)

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2025-06-20 rev1 init. set up files for kicad
2025-06-21 added LED IC's and USB UART bridge
2025-06-21 asdasd
2025-06-23 fixed bus stuff
2025-06-23 bussin
2025-06-23 added memory and fixed gpio pins
2025-07-04 modified power circuitry
2025-07-04 finished first rev of controller schematic minus actually finding passive components. moved some features to rev2 todo
2025-07-06 Moved LEDs around. Replaced some discrete resistors with resistor arrays. Added mounting holes. Added. Added a lot of actual components for passive elements
2025-07-06 ERC good to go. grouped all components on pcb
2025-07-07 fixed 3d models. rounded edges of pcb
2025-07-07 man im tired
2025-07-11 kicad why crash
2025-07-12 save before nuke
2025-07-12 done but need to add stitching vias
2025-07-19 forgor
2025-07-27 clean up DRC. need to add stitching vias and figure out why inner ground plane isnt connected to F.Cu pour
2025-09-02 save before axing motor driver ic's
2025-09-21 axed motor drivers. finished layout for drone but need to review overall system design after reading some stuff
2025-11-19 Removed controller firmware build folder. Added basic LED PWM functionality
2025-11-19 Cleaned up controller firmware dir
2025-11-19 Cleaned files up more. Moduliarized blinky code
